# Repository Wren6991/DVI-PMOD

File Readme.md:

DVI PMOD
--------

This quick and dirty board adapts an HDMI A connector to a 12-pin PMOD expansion port, as found on many FPGA boards. The clock and data lanes are connected to PMOD IOs with 270-ohm series resistors, which gets close to correct CML logic levels from a 3.3V FPGA IO. This is suitable for *DVI* driven from an FPGA, but nominally not enough for HDMI, as the display data channel is not connected. A couple of people have asked me about this board on Twitter, so here are the design files -- go make some!

[PDF schematic here](dvi_pmod.pdf)

I had some of these boards made by JLCPCB (2 layers), and have tried them at up to 372 Mbps (720p 30Hz reduced blanking) on iCEBreaker and iCEstick boards.

Bill of materials:
------------------

* 8x 0402 resistors 270 ohm
* 1x 2.54 mm pin header, 2 ranks of 6 contacts, right-angle
* 1x Stewart SS-53000 HDMI A connector ([Digikey link](https://www.digikey.co.uk/product-detail/en/stewart-connector/SS-53000-001/380-SS-53000-001-ND/10492172))
* Optional 2.54 mm 2 pin header and 0402 capacitor if you need to supply +5V to the Sink

Note that the mechanical drawing provided by Stewart is actually slightly wrong, and shows the contacts offset from the centreline in the wrong direction. The batch of boards I made had this issue, and it was no big deal, just bend the lugs on the HDMI connector to get the contacts to line up with the PCB lands. The version of the board hosted in this repo has a corrected footprint.

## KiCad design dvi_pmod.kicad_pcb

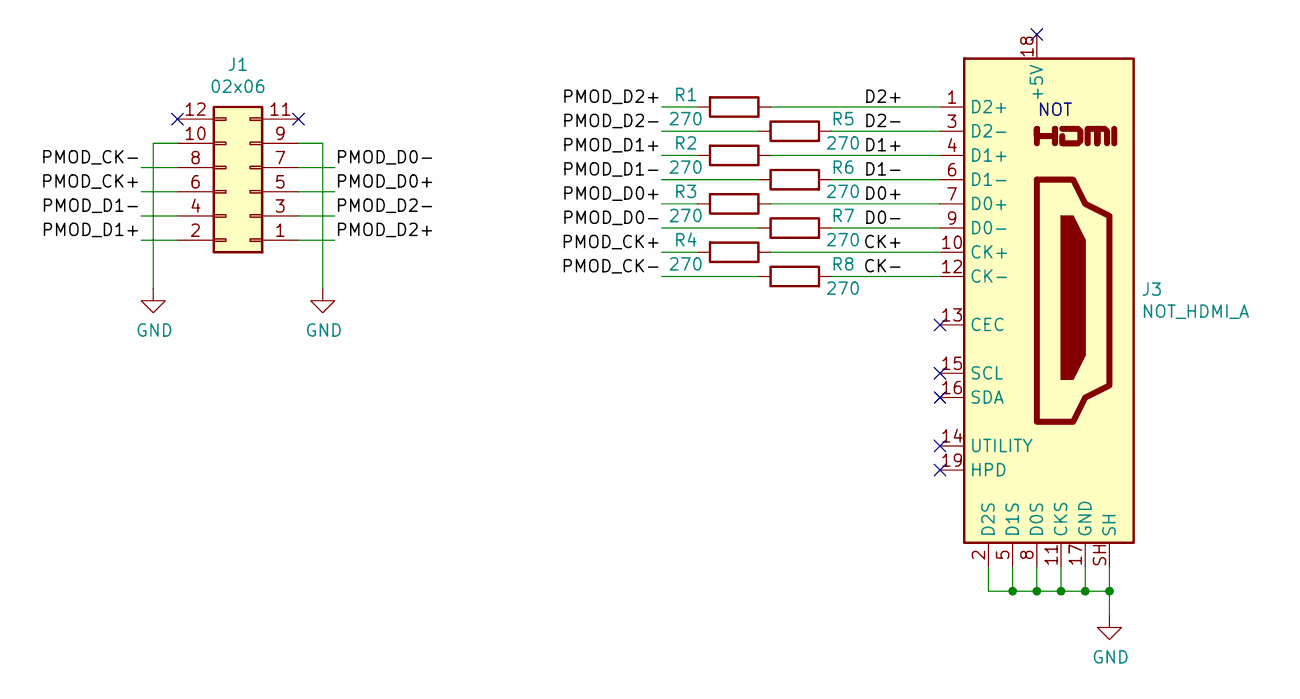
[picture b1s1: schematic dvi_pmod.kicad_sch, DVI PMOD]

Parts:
J1: 02x06; PinSocket_2x06_P2.54mm_Horizontal
J3: NOT_HDMI_A; HDMI-SS-53000
R1, R2, R3, R4, R5, R6, R7, R8: 270; R_0402_1005Metric

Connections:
/CK+: J3.10 (CK+), R4.1
/CK-: J3.12 (CK-), R8.2
/D0+: J3.7 (D0+), R3.1
/D0-: J3.9 (D0-), R7.2
/D1+: J3.4 (D1+), R2.1
/D1-: J3.6 (D1-), R6.2
/D2+: J3.1 (D2+), R1.1
/D2-: J3.3 (D2-), R5.2
/PMOD_CK+: J1.6, R4.2
/PMOD_CK-: J1.8, R8.1
/PMOD_D0+: J1.5, R3.2
/PMOD_D0-: J1.7, R7.1
/PMOD_D1+: J1.2, R2.2
/PMOD_D1-: J1.4, R6.1
/PMOD_D2+: J1.1, R1.2
/PMOD_D2-: J1.3, R5.1
GND: J1.9, J1.10, J3.2 (D2S), J3.5 (D1S), J3.8 (D0S), J3.11 (CKS), J3.17 (GND), J3.SH
no_connect_18: J1.11
no_connect_19: J1.12
no_connect_20: J3.13 (CEC)
no_connect_21: J3.14 (UTILITY)
no_connect_22: J3.15 (SCL)
no_connect_23: J3.16 (SDA)
no_connect_24: J3.18 (+5V)
no_connect_25: J3.19 (HPD)

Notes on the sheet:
NOT

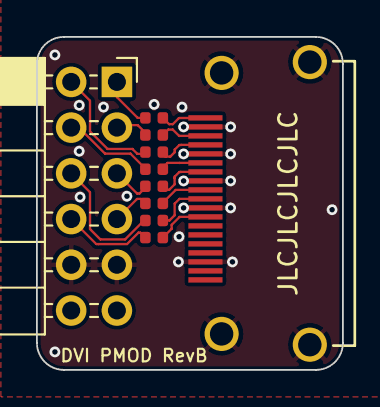
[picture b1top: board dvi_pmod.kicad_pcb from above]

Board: 2 copper layers, 17.0 x 18.5 mm, 10 parts (0 on the bottom side), 17 nets.

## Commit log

2020-10-29 Import
2020-10-31 Add Readme, 3d image
2020-10-31 Create LICENSE
2020-10-31 Oops readme typos
2021-02-02 Rev B board
